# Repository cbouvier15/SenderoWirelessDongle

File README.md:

# SenderoWirelessDongle

EAGLE design for Sendero Wireless Dongle.

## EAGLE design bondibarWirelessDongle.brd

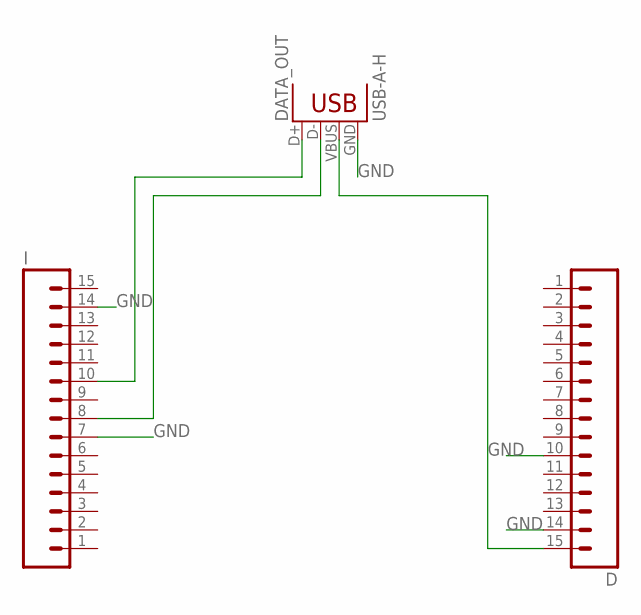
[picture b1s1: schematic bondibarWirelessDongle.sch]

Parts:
D: M15; 1X15
DATA_OUT: USB-A-H
I: M15; 1X15

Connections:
GND: D.10, D.14, DATA_OUT.GND, I.7, I.14
unnamed: D.15, DATA_OUT.VBUS
unnamed: DATA_OUT.D+, I.10
unnamed: DATA_OUT.D-, I.8

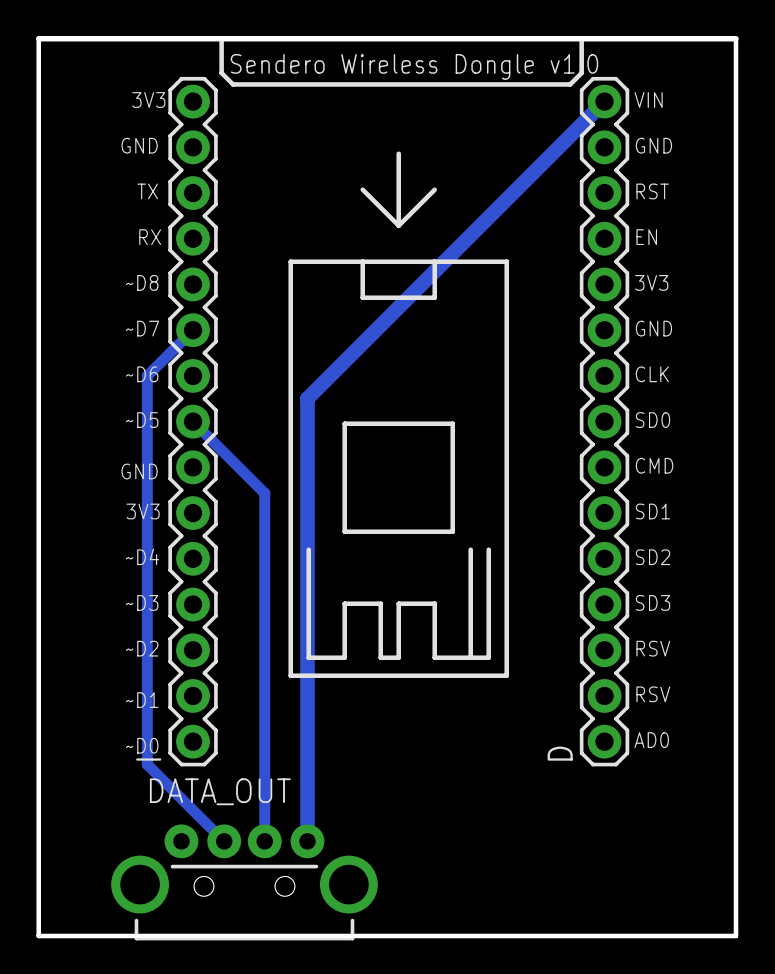
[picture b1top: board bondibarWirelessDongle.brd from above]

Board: 2 copper layers, 38.7 x 49.8 mm, 3 parts (0 on the bottom side), 4 nets.

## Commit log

2016-03-12 Schematics and PCB Layout for V1.0
2016-03-15 Modified version to print in Seedstudio./
2016-03-23 v0.4 - Seedstudio printed version

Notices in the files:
parts and their libraries:
SparkFun-Connectors: Licensing: Creative Commons ShareAlike 4.0 International - https://creativecommons.org/licenses/by-sa/4.0
